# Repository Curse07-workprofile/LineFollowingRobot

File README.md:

# Line-Following Robot - Main PCB

Custom main PCB designed for a university line-following robot project.

I was responsible for the schematic design, component selection, PCB layout, and hardware testing of the main controller board. 
The board integrates an ATmega328P, regulated power, motor switching, analogue line sensors, user input, and ISP programming.

The mechanical platform and control software were developed by other members of the team.

---

---

## Project Overview

The PCB was designed to provide the electrical platform for a small autonomous line-following robot.

### Key requirements

- ATmega328P-based control
- Five analogue reflectance sensors
- Two independently controlled DC motors
- 3.3 V regulated supply
- ISP programming
- User input and status indication
- Reliable operation despite motor-induced supply transients

## My Contribution

I was primarily responsible for the electronics and PCB design:

- Schematic capture and circuit design in KiCad
- Component selection and datasheet research
- Power supply and decoupling design
- Motor driver circuit
- Analogue sensor interface
- ATmega328P peripheral connections
- Crystal oscillator design
- ISP programming interface
- PCB layout and routing
- Hardware assembly and functionality testing
- Component-level debugging and modification

The mechanical chassis and control software were developed by
other members of the team.

## Hardware Architecture

### Microcontroller

**ATmega328P**

The MCU provides:

- ADC inputs for five reflectance sensors
- GPIO for control and status
- SPI for ISP programming
- External 9.216 MHz crystal oscillator

### Power

The board uses a dedicated 3.3 V linear regulator with multiple
levels of decoupling:

- 100 nF local decoupling at MCU supply pins
- 10 µF / 22 µF regulator-side capacitance
- 220 µF bulk capacitance at the battery input

The bulk capacitance was included to reduce supply disturbances
caused by motor current transients.

### Motor Drive

Each motor is controlled using a low-side N-channel MOSFET.

Flyback Schottky diodes provide a current path when the motor
switches off, limiting inductive voltage transients.

### Line Sensors

Five TCRT5000 reflectance sensors provide analogue measurements
through the ATmega328P ADC.

Rather than reducing the sensors to binary black/white states,
the analogue signal was retained to provide the control software
with continuous reflectance information.

## Design Considerations

### Crystal Oscillator

The 9.216 MHz crystal load capacitors were calculated using the
crystal's specified load capacitance and estimated stray
capacitance rather than selecting a standard capacitor value
without calculation.

### ISP Interface

The SPI programming interface includes 330 Ω series resistors on
SCLK, MOSI and MISO.

These were selected to limit transient current while maintaining
appropriate signal levels at the 3.3 V logic voltage.

### PCB Layout

Particular attention was given to separating sensitive analogue
sensor routing from the high-current motor switching paths.

Decoupling capacitors were positioned close to their associated
supply pins, and the ground plane was maintained as continuously
as practical around the sensor circuitry.

## Hardware Bring-Up & Iteration

The first hardware revision provided several useful lessons that
would not have been apparent from schematic or simulation alone.

During bring-up I identified and corrected several issues,
including:

- Status LED initially producing substantially more light than
  intended; the series resistor was recalculated and replaced.
- A power-switch footprint was found to have incorrect pin mapping;
  the physical component was adapted to match the intended circuit.
- Motor supply behaviour highlighted the importance of bulk
  capacitance and supply integrity during high-current transients.

These iterations were useful in demonstrating the difference
between a theoretically correct circuit and a practical PCB
operating in a complete electromechanical system.

## Project Outcome

The PCB itself was successfully assembled and brought up.

However, the complete line-following robot did not achieve the
intended performance. Problems encountered during integration
were primarily associated with the mechanical platform and the
interaction between the electrical and mechanical systems.

This was an important lesson in system-level engineering: a
functional subsystem does not necessarily result in a functional
complete system when mechanical, electrical and software
interfaces are not considered together.

## Skills Demonstrated

- KiCad schematic capture and PCB layout
- ATmega328P embedded hardware
- Mixed analogue/digital PCB design
- Power supply design
- Decoupling and transient management
- MOSFET motor switching
- Flyback protection
- Analogue sensor interfacing
- ADC design
- SPI / ISP programming
- Datasheet-based component selection
- Circuit calculations
- Hardware bring-up and debugging
- PCB fabrication and assembly
- System-level engineering

## Resources

- [KiCad Schematic](./images/full_skem.png)
- [PCB Layout](./images/fullPCB.png)
- [PCB Design Files](./PCB_design/)
- [Board Photos](./board.md)
- [Project Report](./LFR_report.pdf)

---
*Developed as part of a university group project. Main PCB design and electronics by myself (Curtis Christian); other tasks covered in the report are done as collabarative effort by our group.*

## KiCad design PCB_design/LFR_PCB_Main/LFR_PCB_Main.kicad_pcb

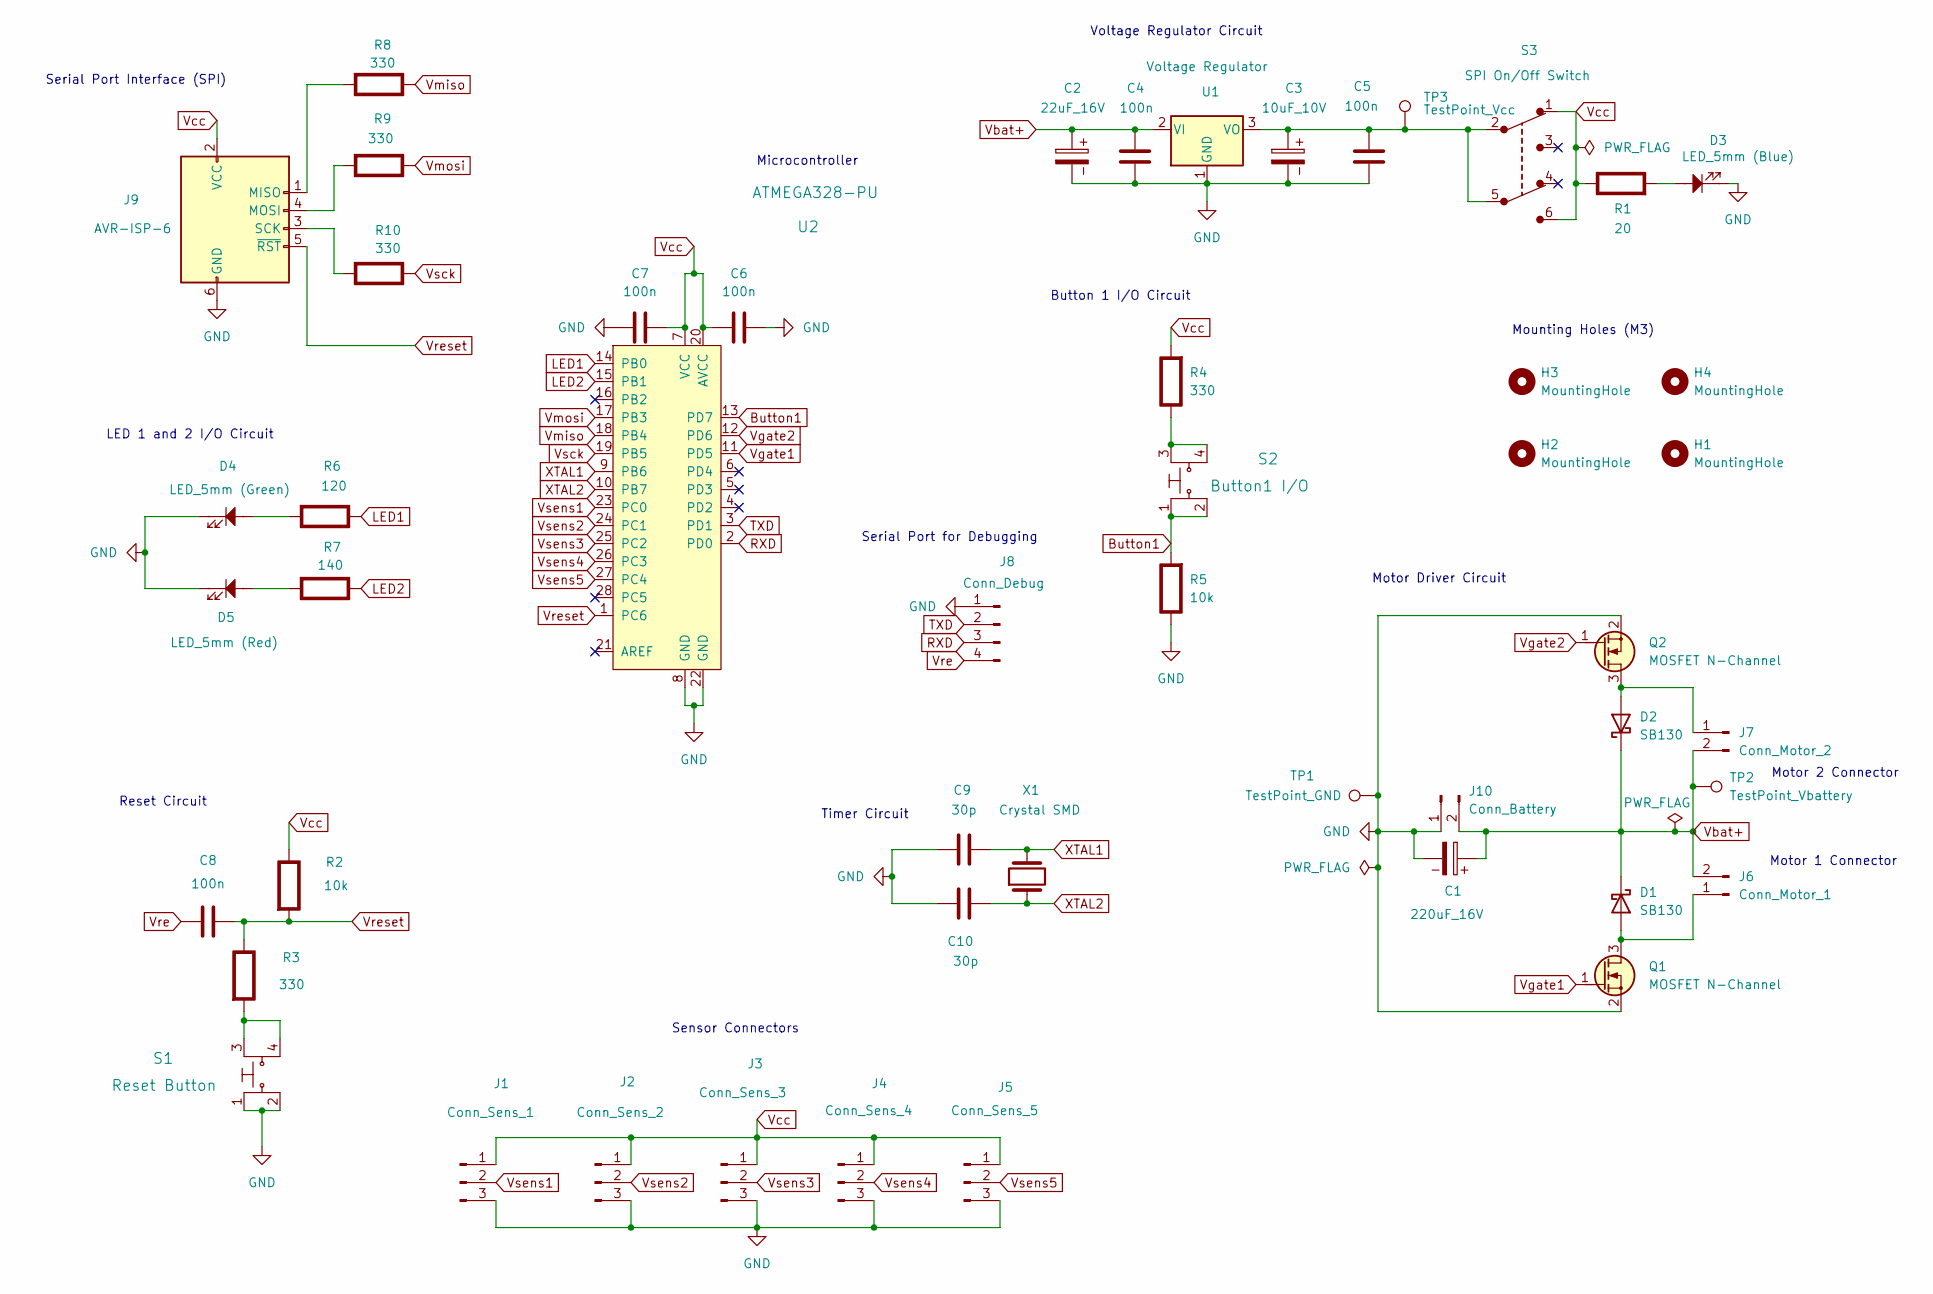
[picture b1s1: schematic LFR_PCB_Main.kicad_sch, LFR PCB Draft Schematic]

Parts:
C1: 220uF_16V; CP_Radial_D6.3mm_P2.50mm
C2: 22uF_16V; CP_Radial_D5.0mm_P2.00mm
C3: 10uF_10V; CP_Radial_D5.0mm_P2.00mm
C4, C5, C6, C7, C8: 100n; C_1206_3216Metric_Pad1.33x1.80mm_HandSolder
C9, C10: 30p; C_1206_3216Metric_Pad1.33x1.80mm_HandSolder
D1, D2: SB130; D_DO-41_SOD81_P10.16mm_Horizontal
D3: LED_5mm (Blue); LED_D5.0mm
D4: LED_5mm (Green); LED_D5.0mm
D5: LED_5mm (Red); LED_D5.0mm
H1, H2, H3, H4: MountingHole; MountingHole_3.2mm_M3
J1: Conn_Sens_1; PinHeader_1x03_P2.54mm_Vertical
J2: Conn_Sens_2; PinHeader_1x03_P2.54mm_Vertical
J3: Conn_Sens_3; PinHeader_1x03_P2.54mm_Vertical
J4: Conn_Sens_4; PinHeader_1x03_P2.54mm_Vertical
J5: Conn_Sens_5; PinHeader_1x03_P2.54mm_Vertical
J6: Conn_Motor_1; PinHeader_1x02_P2.54mm_Vertical
J7: Conn_Motor_2; PinHeader_1x02_P2.54mm_Vertical
J8: Conn_Debug; PinHeader_1x04_P2.54mm_Vertical
J9: AVR-ISP-6; IDC-Header_2x03_P2.54mm_Vertical
J10: Conn_Battery; PinHeader_1x02_P2.54mm_Vertical
Q1, Q2: MOSFET N-Channel; SC-59
R1: 20; R_0805_2012Metric_Pad1.20x1.40mm_HandSolder; Rating W
R2, R5: 10k; R_Axial_DIN0309_L9.0mm_D3.2mm_P12.70mm_Horizontal; Rating W
R3, R4, R8, R9, R10: 330; R_0805_2012Metric_Pad1.20x1.40mm_HandSolder; Rating W
R6: 120; R_0805_2012Metric_Pad1.20x1.40mm_HandSolder; Rating W
R7: 140; R_0805_2012Metric_Pad1.20x1.40mm_HandSolder; Rating W
S1: Reset Button; Switch_Tactile_THT_6x6mm_MJTP1230; MPN MJTP1230; Digi-Key_PN 679-2428-ND
S2: Button1 I/O; Switch_Tactile_THT_6x6mm_MJTP1230; MPN MJTP1230; Digi-Key_PN 679-2428-ND
S3: SPI On/Off Switch; SWITCH_011CQN; MPN JS202011SCQN; Digi-Key_PN 401-2002-1-ND
TP1: TestPoint_GND; TestPoint_Pad_D2.0mm
TP2: TestPoint_Vbattery; TestPoint_Pad_D2.0mm
TP3: TestPoint_Vcc; TestPoint_Pad_D2.0mm
U1: Voltage Regulator; TO-92_Inline
U2: ATMEGA328-PU; DIP-28_W7.62mm; MPN ATMEGA328-PU; Digi-Key_PN ATMEGA328-PU-ND
X1: Crystal SMD; Crystal_SMD_HC49-SD

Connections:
Button1: R5.2 (-), S2.1, S2.2, U2.13 (PD7)
GND: C1.2, C2.2, C3.2, C4.2, C5.2, C6.2, C7.1, C9.1, C10.1, D3.1, D4.1, D5.1, J1.3, J2.3, J3.3, J4.3, J5.3, J8.1, J9.6 (GND), J10.1, Q1.2 (S), Q2.2 (S), R5.1 (+), S1.1, S1.2, TP1.1, U1.1 (GND), U2.8 (GND), U2.22 (GND)
LED1: R6.1 (+), U2.14 (PB0)
LED2: R7.1 (+), U2.15 (PB1)
unnamed: D1.2 (A), J6.1, Q1.3 (D)
unnamed: D2.2 (A), J7.1, Q2.3 (D)
unnamed: J9.1 (MISO), R8.2 (-)
unnamed: J9.4 (MOSI), R9.2 (-)
unnamed: J9.3 (SCK), R10.2 (-)
unnamed: D3.2, R1.2 (-)
unnamed: R3.2 (-), S1.3, S1.4
unnamed: R4.1 (+), S2.3, S2.4
unnamed: D4.2, R6.2 (-)
unnamed: D5.2, R7.2 (-)
unnamed: C3.1, C5.1, S3.2, S3.5, TP3.1, U1.3 (VO)
RXD: J8.3, U2.2 (PD0)
TXD: J8.2, U2.3 (PD1)
Vbat+: C1.1, C2.1, C4.1, D1.1 (K), D2.1 (K), J6.2, J7.2, J10.2, TP2.1, U1.2 (VI)
Vcc: C6.1, C7.2, J1.1, J2.1, J3.1, J4.1, J5.1, J9.2 (VCC), R1.1 (+), R2.1 (+), R4.2 (-), S3.1, S3.6, U2.7 (VCC), U2.20 (AVCC)
Vgate1: Q1.1 (G), U2.11 (PD5)
Vgate2: Q2.1 (G), U2.12 (PD6)
Vmiso: R8.1 (+), U2.18 (PB4)
Vmosi: R9.1 (+), U2.17 (PB3)
Vre: C8.1, J8.4
Vreset: C8.2, J9.5 (~RST), R2.2 (-), R3.1 (+), U2.1 (PC6)
Vsck: R10.1 (+), U2.19 (PB5)
Vsens1: J1.2, U2.23 (PC0)
Vsens2: J2.2, U2.24 (PC1)
Vsens3: J3.2, U2.25 (PC2)
Vsens4: J4.2, U2.26 (PC3)
Vsens5: J5.2, U2.27 (PC4)
XTAL1: C9.2, U2.9 (PB6), X1.2
XTAL2: C10.2, U2.10 (PB7), X1.1

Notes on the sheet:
Motor Driver Circuit
Reset Circuit
Timer Circuit
Sensor Connectors
Button 1 I/O Circuit
LED 1 and 2 I/O Circuit
Voltage Regulator Circuit
Mounting Holes (M3)
Microcontroller
Serial Port Interface (SPI)
Motor 2 Connector
Motor 1 Connector
Serial Port for Debugging

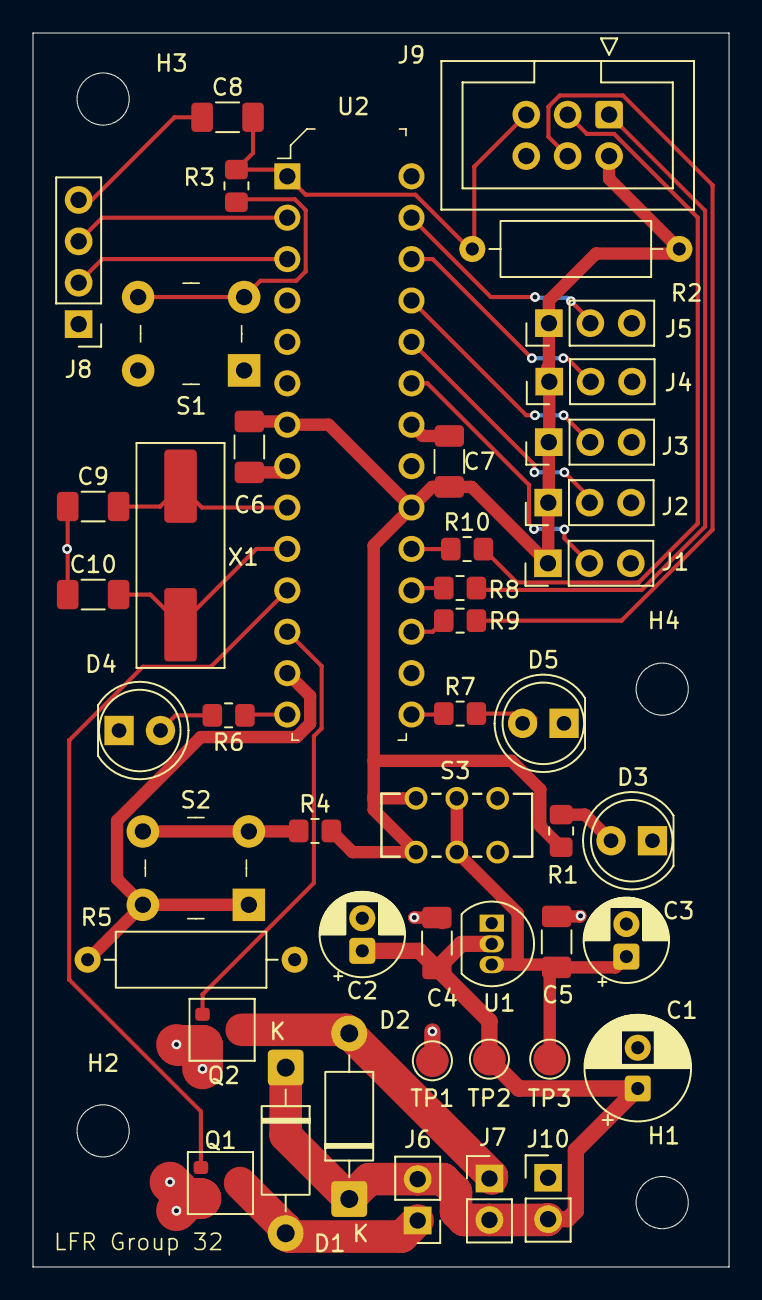
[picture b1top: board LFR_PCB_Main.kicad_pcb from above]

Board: 2 copper layers, 42.7 x 75.7 mm, 50 parts (0 on the bottom side), 33 nets.

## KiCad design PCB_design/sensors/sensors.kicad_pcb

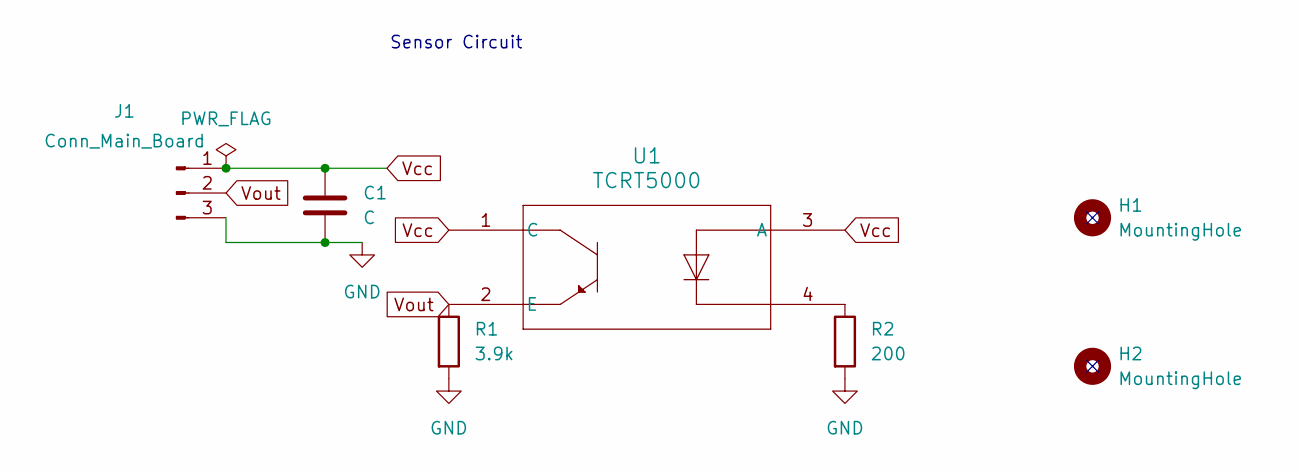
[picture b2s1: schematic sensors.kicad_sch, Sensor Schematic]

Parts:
C1: C; C_1206_3216Metric_Pad1.33x1.80mm_HandSolder
H1, H2: MountingHole; MountingHole_3.2mm_M3
J1: Conn_Main_Board; PinHeader_1x03_P2.54mm_Vertical
R1: 3.9k; R_Axial_DIN0207_L6.3mm_D2.5mm_P7.62mm_Horizontal
R2: 200; R_Axial_DIN0207_L6.3mm_D2.5mm_P7.62mm_Horizontal
U1: TCRT5000; OPTO_TCRT5000

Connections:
GND: C1.2, J1.3, R1.2, R2.2
unnamed: R2.1, U1.4
Vcc: C1.1, J1.1, U1.1 (C), U1.3 (A)
Vout: J1.2, R1.1, U1.2 (E)

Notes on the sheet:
Sensor Circuit

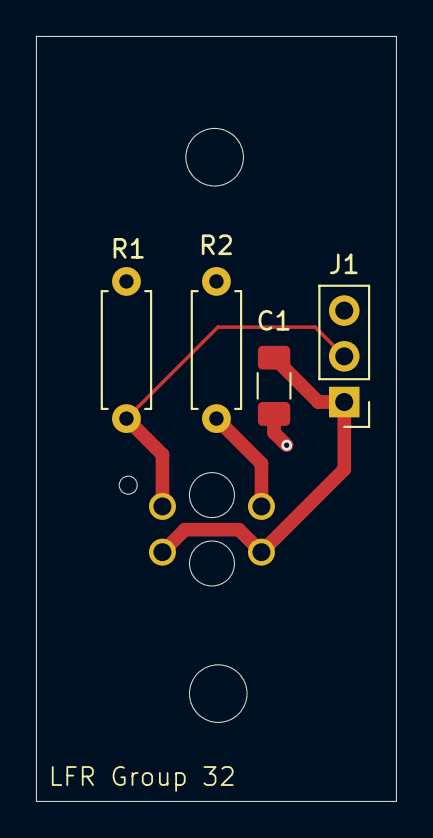
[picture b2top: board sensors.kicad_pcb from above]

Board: 2 copper layers, 20.0 x 42.5 mm, 7 parts (1 on the bottom side), 4 nets.

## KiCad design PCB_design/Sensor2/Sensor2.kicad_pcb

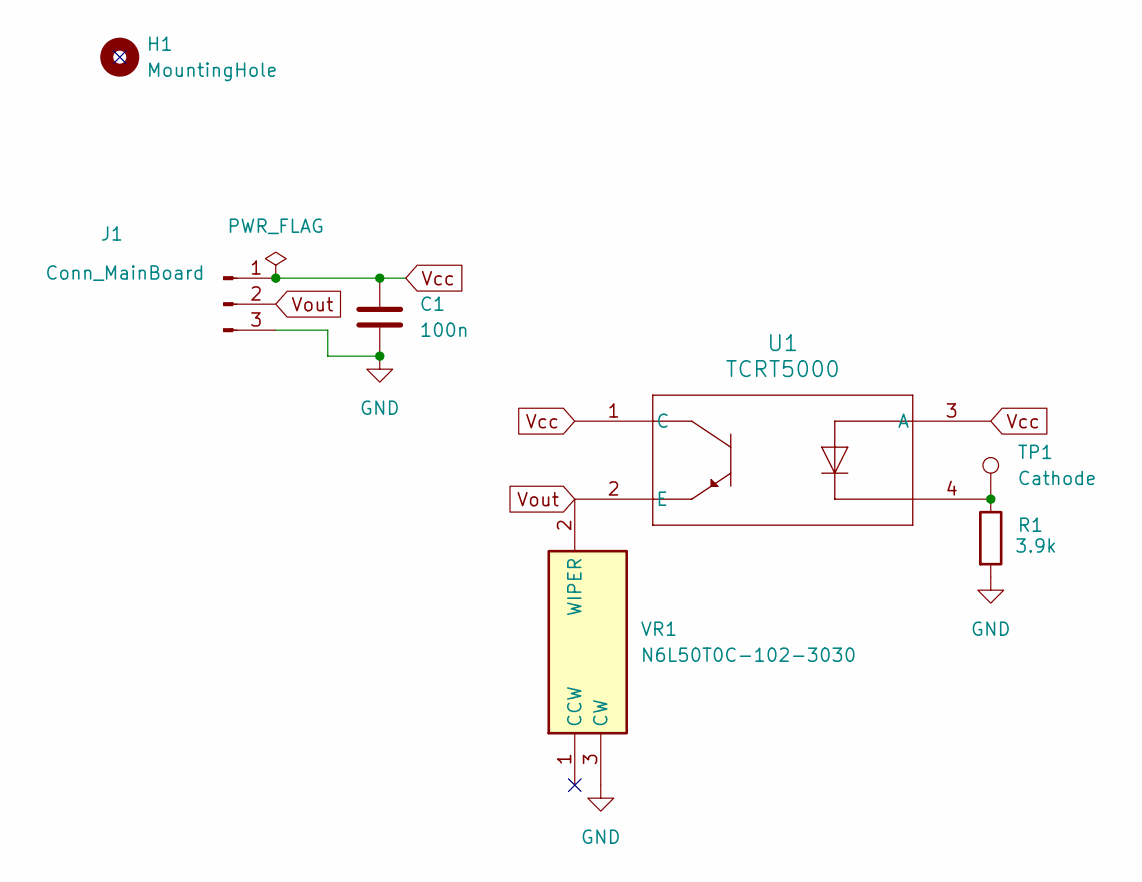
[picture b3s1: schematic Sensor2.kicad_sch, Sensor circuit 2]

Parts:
C1: 100n; C_1206_3216Metric_Pad1.33x1.80mm_HandSolder
H1: MountingHole; MountingHole_3.2mm_M3
J1: Conn_MainBoard; PinHeader_1x03_P2.54mm_Vertical
R1: 3.9k; R_0805_2012Metric_Pad1.20x1.40mm_HandSolder
TP1: Cathode; TestPoint_Plated_Hole_D2.0mm
U1: TCRT5000; OPTO_TCRT5000
VR1: N6L50T0C-102-3030; N6L50T0C1033030; Mouser Part Number 531-N6L50T0C103-3030

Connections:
GND: C1.2, J1.3, R1.2, VR1.3 (CW)
unnamed: R1.1, TP1.1, U1.4
Vcc: C1.1, J1.1, U1.1 (C), U1.3 (A)
Vout: J1.2, U1.2 (E), VR1.2 (WIPER)

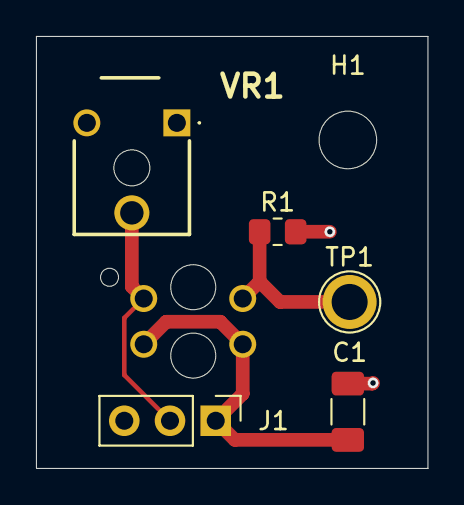
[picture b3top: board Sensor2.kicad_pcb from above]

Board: 2 copper layers, 21.8 x 24.0 mm, 7 parts (1 on the bottom side), 4 nets.

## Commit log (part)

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2025-09-22 PCB design
2025-09-28 More complete version
